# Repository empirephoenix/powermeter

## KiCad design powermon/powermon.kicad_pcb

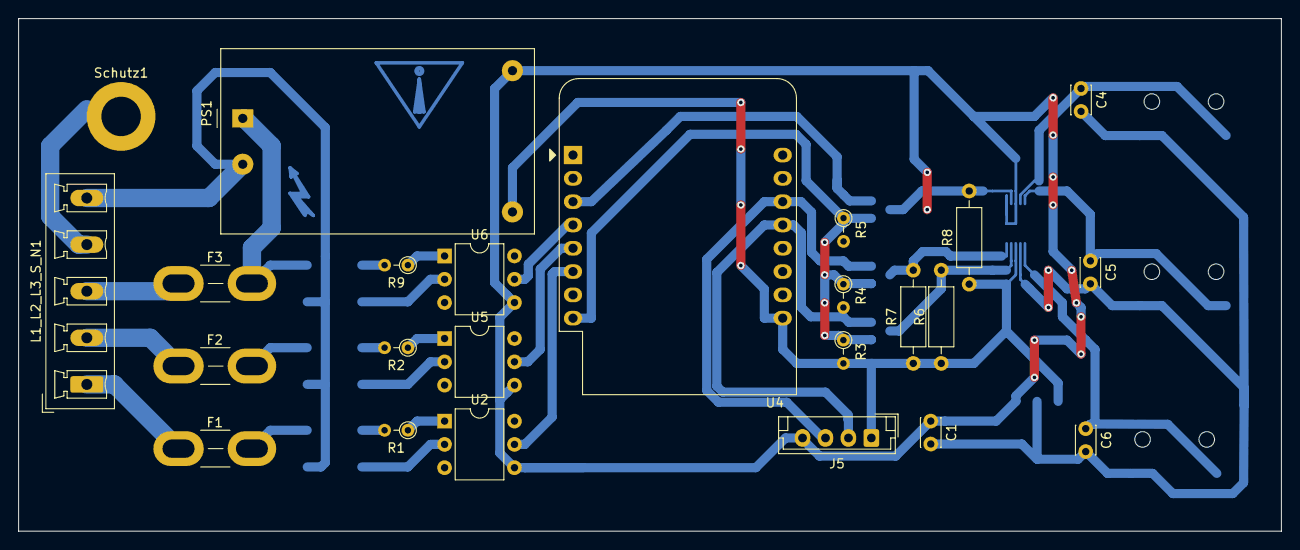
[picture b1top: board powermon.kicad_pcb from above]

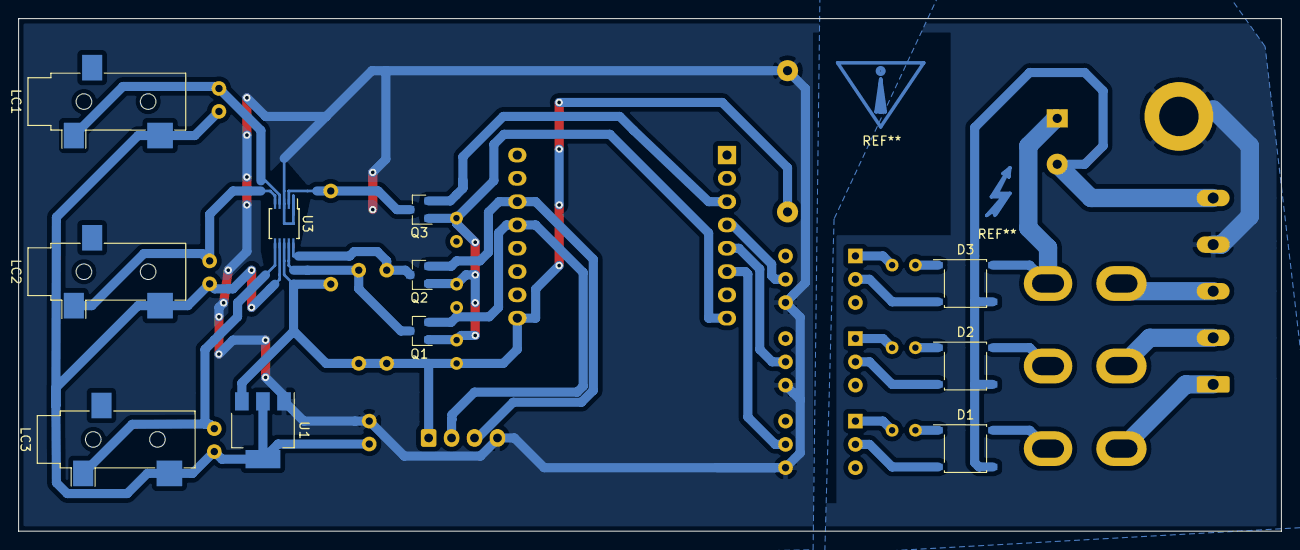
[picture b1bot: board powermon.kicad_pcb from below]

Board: 2 copper layers, 137.7 x 55.9 mm, 35 parts (11 on the bottom side), 33 nets.

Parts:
C1, C4, C5, C6: 1uF; C_Disc_D3.0mm_W2.0mm_P2.50mm
D1, D2, D3: ABS10; Diode_Bridge_Diotec_ABS
F1, F2, F3: Fuse_Small; Fuse_Blade_Mini_directSolder
J5: i2c_LCD; JST_EH_B4B-EH-A_1x04_P2.50mm_Vertical
L1_L2_L3_S_N1: L1 L2 L3 S N; PhoenixContact_MCV_1,5_5-G-5.08_1x05_P5.08mm_Vertical
LC1, LC2, LC3: AudioJack3; Jack_3.5mm_CUI_SJ-3523-SMT_Horizontal
PS1: HLK-PM01; Converter_ACDC_HiLink_HLK-PMxx
Q1, Q2, Q3: BSS138; SOT-23
R1, R2, R9: 12K; R_Axial_DIN0204_L3.6mm_D1.6mm_P2.54mm_Vertical
R3, R4, R5: 10K; R_Axial_DIN0204_L3.6mm_D1.6mm_P2.54mm_Vertical
R6, R7, R8: 10K; R_Axial_DIN0207_L6.3mm_D2.5mm_P10.16mm_Horizontal
Schutz1: Conn_01x01_Female; MountingHole_4.3mm_M4_DIN965_Pad
U1: AMS1117-2.5; SOT-223-3_TabPin2
U2, U5, U6: CNY17-3; DIP-6_W7.62mm
U3: ADS1115IDGS; TSSOP-10_3x3mm_P0.5mm
U4: WeMos_D1_mini; WEMOS_D1_mini_light

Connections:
2_5V: C1.2, C4.2, C5.2, C6.2, LC1.T, LC2.T, LC3.T, U1.2, U3.7
3_3V: Q1.1, Q2.1, Q3.1, R3.1, R4.1, R5.1, U4.8
5V: J5.1, PS1.4, R6.1, R7.1, R8.1, U1.3, U3.8, U4.9
GND: C1.1, J5.4, PS1.3, U1.1, U2.4, U3.1, U3.3, U4.10, U5.4, U6.4
H_RDY: Q3.3, R8.2, U3.2
H_SCL: Q2.3, R7.2, U3.10
H_SDA: Q1.3, R6.2, U3.9
L1: D1.4, F1.2
L1NULL: U2.5, U4.6
L1_C: C4.1, LC1.S, U3.4
L2: D2.4, F2.2
L2NULL: U4.5, U5.5
L2_C: C5.1, LC2.S, U3.5
L3: D3.4, F3.2, PS1.1
L3NULL: U4.4, U6.5
L3_C: C6.1, LC3.S, U3.6
N: D1.3, D2.3, D3.3, L1_L2_L3_S_N1.5, PS1.2
unnamed: D1.1, R1.2
unnamed: D1.2, U2.2
unnamed: D2.1, R2.2
unnamed: D2.2, U5.2
unnamed: D3.1, R9.2
unnamed: D3.2, U6.2
unnamed: F1.1, L1_L2_L3_S_N1.1
unnamed: F2.1, L1_L2_L3_S_N1.2
unnamed: F3.1, L1_L2_L3_S_N1.3
unnamed: L1_L2_L3_S_N1.4, Schutz1.1
unnamed: R1.1, U2.1
unnamed: R2.1, U5.1
unnamed: R9.1, U6.1
RDY: Q3.2, R5.2, U4.3
SCL: J5.3, Q2.2, R4.2, U4.14
SDA: J5.2, Q1.2, R3.2, U4.13

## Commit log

2020-12-22 initial version
